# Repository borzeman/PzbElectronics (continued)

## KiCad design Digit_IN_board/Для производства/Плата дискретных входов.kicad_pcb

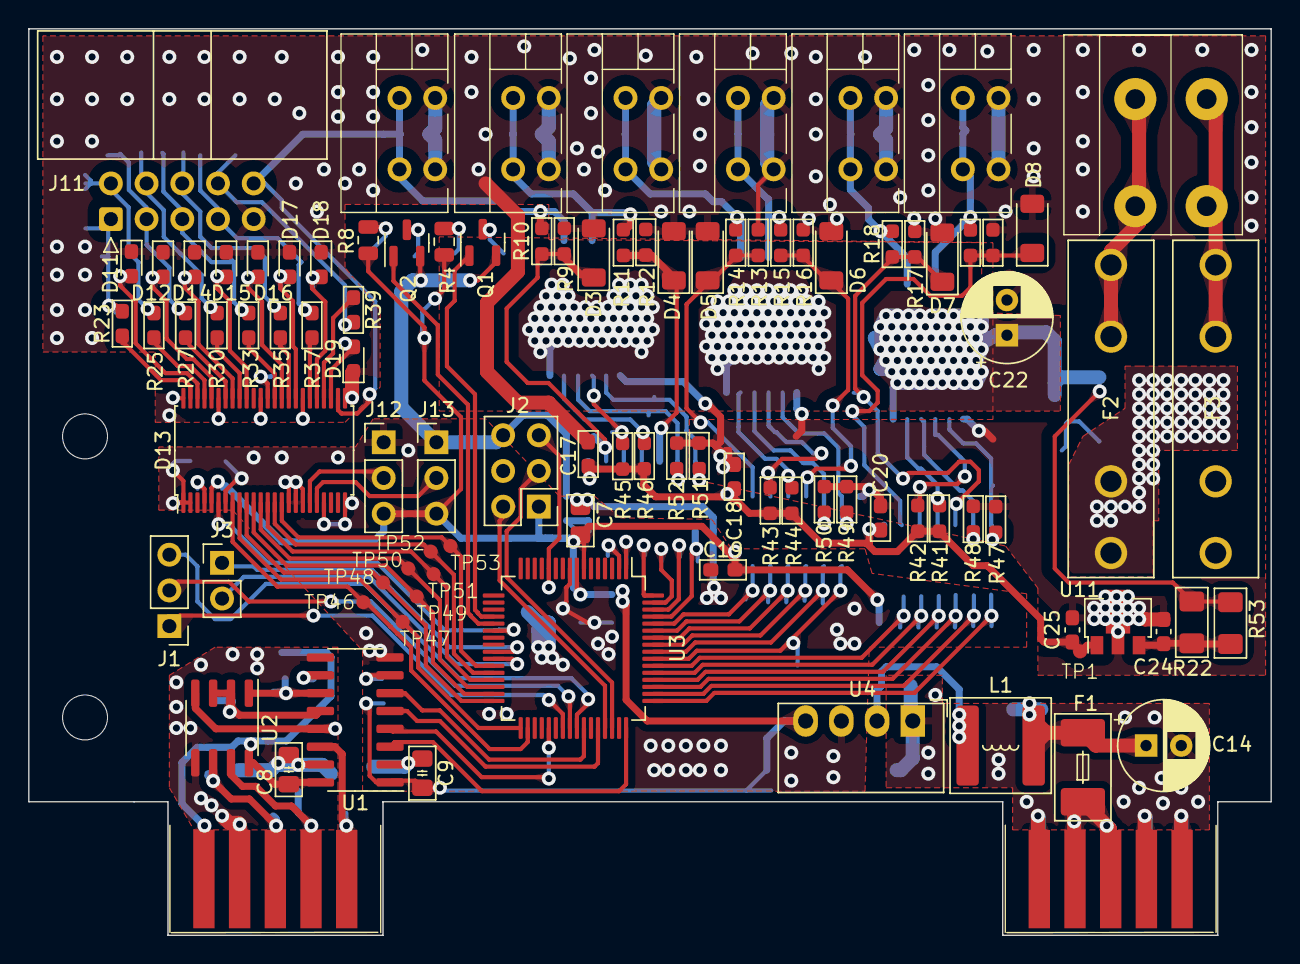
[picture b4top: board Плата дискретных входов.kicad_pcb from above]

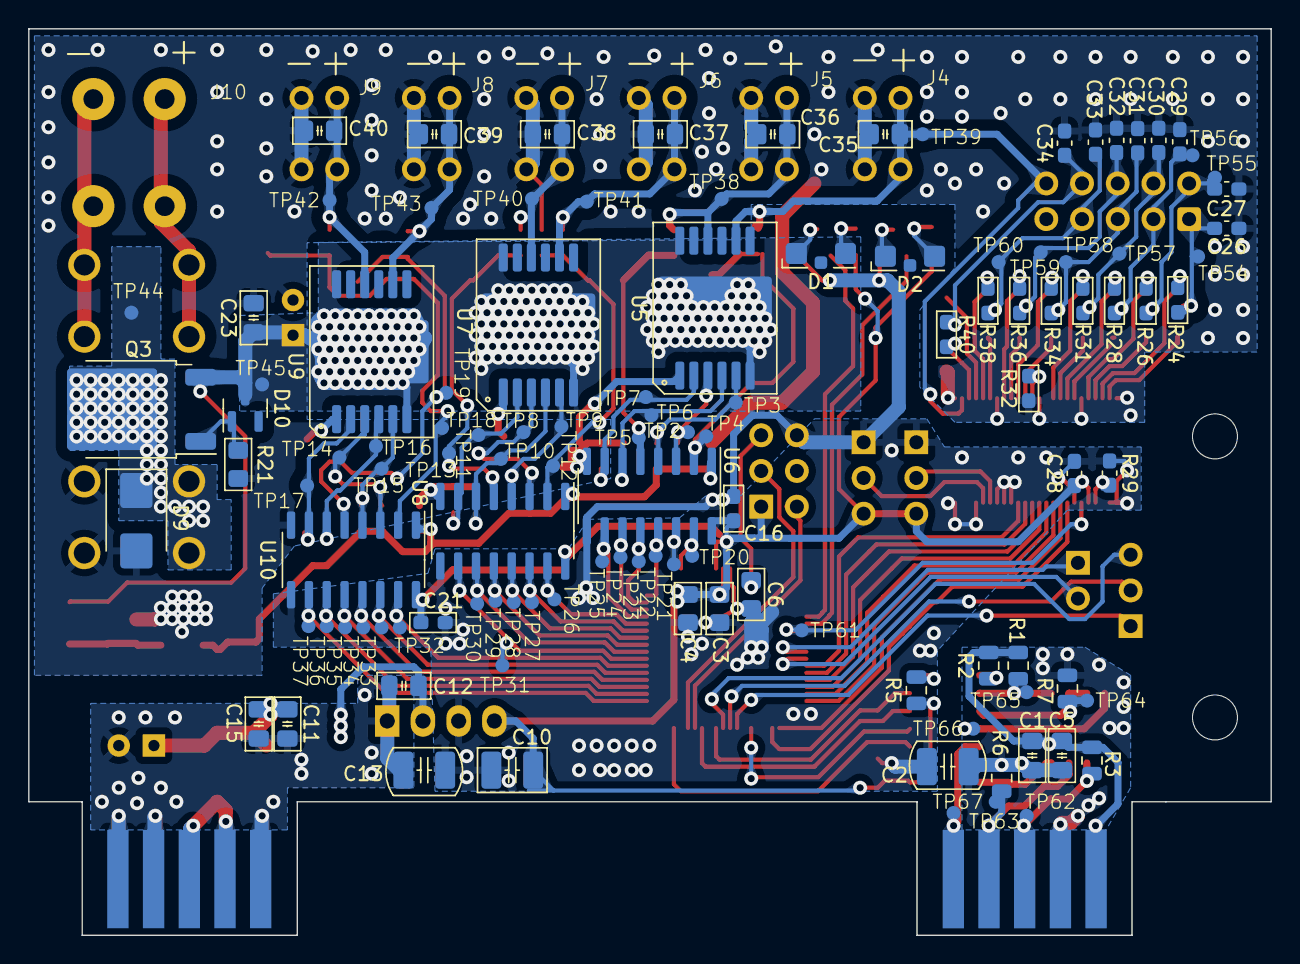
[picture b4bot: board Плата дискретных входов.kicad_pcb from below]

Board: 2 copper layers, 88.4 x 64.5 mm, 214 parts (115 on the bottom side), 121 nets.

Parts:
C1: 1uF 100V 0805; C_0805_2012Metric_Pad1.18x1.45mm_HandSolder
C2, C13: 270 pf X7R 1206 2000v 202R18W271KW4E; C_1210_3225Metric_Pad1.42x2.65mm
C3, C6, C7: 0,1uF 100V 0805; R_0805_2012Metric_Pad1.20x1.40mm_HandSolder
C4: 4,7uF 50V 0805; R_0805_2012Metric_Pad1.20x1.40mm_HandSolder
C5, C8, C9, C15, C23, C35, C36, C37, C38, C39, C40: 0,1uF 100V 0805; C_0805_2012Metric_Pad1.18x1.45mm_HandSolder
C10: 10uF 50V 1210 GRM32ER71H106K; C_1210_3225Metric_Pad1.42x2.65mm_HandSolder
C11, C12: 4,7uF 50V 0805; C_0805_2012Metric_Pad1.18x1.45mm_HandSolder
C14, C22: 47uF 63V D10,5; CP_Radial_D6.3mm_P2.50mm
C16, C17, C18, C19, C20, C21, C25, C26, C27, C29, C30, C31, C32, C33, C34: 0,1uF 100V 0603; C_0603_1608Metric_Pad1.08x0.95mm_HandSolder
C24, C28: 0,33uF 50V 0603; C_0603_1608Metric_Pad1.08x0.95mm_HandSolder
D1, D2: KPA-3010CGCK; LED_Kingbright_KPA-3010_3x2x1mm
D3, D4, D5, D6, D7, D8: BZV55B5V1; D_MiniMELF
D9: SM6T30A (SMB); D_SMB
D10: BZX84C10 (SOT-23); SOT-23
D11, D12, D14, D15, D16, D17, D18, D19: LED 0603 (FYLS-0603UWC); LED_0603_1608Metric_Pad1.05x0.95mm_HandSolder
D13: ISO1I811T; TSSOP-48_6.1x12.5mm_P0.5mm
F1: 045201.5MRL; Fuse_Littelfuse-NANO2-451_453
F2, F3: Fuse 5A ZH266 (2 клипсы); Fuseholder_100_series_5x20mm_D1,5
H1, H2: MountingHole; MountingHole_3.2mm_M3
J1: DebugUSART (PinHeader_01x03_P2.54mm); PinHeader_1x03_P2.54mm_Vertical
J2: Prog (PinHeader_2x03_P2.54mm); PinHeader_2x03_P2.54mm_Vertical
J3: Debug GPIO (PinHeader_01x02_P2.54mm); PinHeader_1x02_P2.54mm_Vertical
J4, J5, J6, J7, J8, J9: DG141R-02
J10: DG142R-5.08-02P-14
J11: DS1013-01-10RSiB-B (1); IDC-Header_2x05_P2.54mm_Horizontal
J12, J13: DS0; PinHeader_1x03_P2.54mm_Vertical
L1: 6,8uH 3,5A ETQP3M6R8KVP; L_Bourns-SRN6028
Q1, Q2: DTC114ECA (SOT-23); SOT-23
Q3: IRFR5305 (TO-252-2); TO-252-2
R1, R7: 0805-10 кОм±5%-0,125 Вт; R_0805_2012Metric
R2, R5: 0805-4,7 кОм±5%-0,125 Вт; R_0805_2012Metric
R3, R6: 0805-560 Ом±5%-0,125 Вт; R_0805_2012Metric
R4, R8: 0805-150 Ом±5%-0,125 Вт; R_0805_2012Metric
R9, R13, R17: 0603-3 кОм±5%-0,062 Вт; R_0603_1608Metric_Pad0.98x0.95mm_HandSolder
R10, R11, R14, R15, R18, R19: 0603-12 кОм±5%-0,062 Вт; R_0603_1608Metric_Pad0.98x0.95mm_HandSolder
R12, R16, R20, R41, R42, R43, R44, R45, R46, R47, R48, R49, R50, R51, R52: 0603-10 кОм±5%-0,062 Вт; R_0603_1608Metric_Pad0.98x0.95mm_HandSolder
R21: 0805-10 кОм±5%-0,125 Вт; R_0805_2012Metric_Pad1.20x1.40mm_HandSolder
R22: 1206-620 Ом±5%-0,25 Вт; R_1206_3216Metric_Pad1.42x1.75mm_HandSolder
R23, R25, R27, R30, R33, R35, R37, R39: 0603-2 кОм±5%-0,062 Вт; R_0603_1608Metric_Pad1.05x0.95mm_HandSolder
R24, R26, R28, R31, R34, R36, R38, R40: 0603-12 кОм±5%-0,062 Вт; R_0603_1608Metric_Pad1.05x0.95mm_HandSolder
R29: 0603-200 кОм±5%-0,062 Вт; C_0603_1608Metric_Pad1.08x0.95mm_HandSolder
R32: 0603-33 Ом±5%-0,062 Вт; R_0603_1608Metric_Pad1.05x0.95mm_HandSolder
R53: OPT; R_1206_3216Metric_Pad1.42x1.75mm_HandSolder
RS1, RS2: SL-10 (L-KLS1-603C-10-S); Edge_Conn_KLS1-603-10
TP1, TP2, TP3, TP4, TP5, TP6, TP7, TP8, TP9, TP10, TP11, TP12, TP13, TP14, TP15, TP16, TP17, TP18, TP19, TP20, TP21, TP22, TP23, TP24, TP25, TP26, TP27, TP28, TP29, TP30, TP31, TP32, TP33, TP34, TP35, TP36, TP37, TP38, TP39, TP40, TP41, TP42, TP43, TP44, TP45, TP46, TP47, TP48, TP49, TP50, TP51, TP52, TP53, TP54, TP55, TP56, TP57, TP58, TP59, TP60, TP61, TP62, TP63, TP64, TP65, TP66, TP67: TestPoint_D1
U1: pia141M30 (SOIC-16); SOIC-16_3.9x9.9mm_P1.27mm
U2: ADM3485EARZ-REEL (SOIC-8); SOIC-8_3.9x4.9mm_P1.27mm
U3: STM32G070RBTx (LQFP-64); LQFP-64_10x10mm_P0.5mm
U4: AM1SS-2403SJZ; Converter_DCDC_Murata_MEE1SxxxxSC_THT
U5: BTS5215 (DSO-12-9); Infineon_PG-DSO-12-9
U6, U8, U10: pia162M30 (SOIC-16); SOIC-16_3.9x9.9mm_P1.27mm
U7, U9: BTS5215; Infineon_PG-DSO-12-9
U11: L78L05 (SOT89-3); SOT-89-3

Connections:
+3V3: C3.1, C4.1, C7.1, C9.2, C10.1, C16.2, C19.2, C21.2, C28.1, D13.5 (VCC), J2.1, J12.3, J13.3, R4.2, R5.1, R8.1, U1.1 (VDD1), U3.7 (VREF+), U3.8 (VDD), U4.4 (OUT+), U6.16 (VDD2), U8.16 (VDD2), U10.16 (VDD2)
+5V: C17.2, C18.2, C20.2, C25.1, R41.1, R42.2, R43.2, R44.1, R45.2, R46.1, TP1.1, U6.1 (VDD1), U8.1 (VDD1), U10.1 (VDD1), U11.1 (OUT)
+24V: C11.1, C14.1, C15.1, F1.2, L1.1
/+3.3VRS485: C1.2, C5.2, C8.2, R1.2, R2.2, R3.2, RS1.1, RS1.10, U1.16 (VDD2), U2.8 (VCC)
/+24_FT_1: C35.2, D13.26 (VBB), J4.2, J11.10, R10.2, TP39.1, U5.8 (OUT2)
/D0: D13.8 (D0), TP46.1, U3.34 (PB14)
/D1: D13.9 (D1), TP47.1, U3.33 (PB13)
/D2: D13.10 (D2), TP48.1, U3.32 (PB12)
/D3: D13.11 (D3), TP49.1, U3.31 (PB11)
/D4: D13.12 (D4), TP50.1, U3.30 (PB10)
/D5: D13.13 (D5), TP51.1, U3.29 (PB2)
/D6: D13.14 (D6), TP52.1, U3.28 (PB1)
/D7: D13.15 (D7), TP53.1, U3.27 (PB0)
/DE_USART_1: U1.5 (VIC), U3.44 (PA12/PA10)
/Descret Input/OUT1_1: C26.1, J11.1, R23.2, R24.1, TP54.1
/Descret Input/OUT1_2: C27.1, J11.2, R25.2, R26.1, TP55.1
/Descret Input/OUT1_3: C29.1, J11.3, R27.2, R28.1, TP56.1
/Descret Input/OUT1_4: C30.1, J11.4, R30.2, R31.1, TP57.1
/Descret Input/OUT1_5: C31.1, J11.5, R33.2, R34.1, TP58.1
/Descret Input/OUT1_6: C32.1, J11.6, R35.2, R36.1, TP59.1
/Descret Input/OUT1_7: C33.1, J11.7, R37.2, R38.1, TP60.1
/Descret Input/OUT1_8: C34.1, J11.8, R39.2, R40.1
/Descret Input/OUT1_H: D13.47 (I7H), R23.1
/Descret Input/OUT1_L: D11.2 (A), D13.46 (I7L), R24.2
/Descret Input/OUT2_H: D13.45 (I6H), R25.1
/Descret Input/OUT2_L: D12.2 (A), D13.44 (I6L), R26.2
/Descret Input/OUT3_H: D13.42 (I5H), R27.1
/Descret Input/OUT3_L: D13.41 (I5L), D14.2 (A), R28.2
/Descret Input/OUT4_H: D13.40 (I4H), R30.1
/Descret Input/OUT4_L: D13.39 (I4L), D15.2 (A), R31.2
/Descret Input/OUT5_H: D13.35 (I3H), R33.1
/Descret Input/OUT5_L: D13.34 (I3L), D16.2 (A), R34.2
/Descret Input/OUT6_H: D13.33 (I2H), R35.1
/Descret Input/OUT6_L: D13.32 (I2L), D17.2 (A), R36.2
/Descret Input/OUT7_H: D13.30 (I1H), R37.1
/Descret Input/OUT7_L: D13.29 (I1L), D18.2 (A), R38.2
/Descret Input/OUT8_H: D13.28 (I0H), R39.1
/Descret Input/OUT8_L: D13.27 (I0L), D19.2 (A), R40.2
/DiscretOut/24V_OUT: C22.1, C23.1, D10.3 (K), Q3.3 (S), R22.2, R53.2, TP45.1, U5.6 (VBB), U5.12 (VBB), U5.13 (VBB), U7.6 (VBB), U7.12 (VBB), U7.13 (VBB), U9.6 (VBB), U9.12 (VBB), U9.13 (VBB)
/DiscretOut/IN1: R52.2, TP6.1, U5.4 (IN2), U6.6 (VOE)
/DiscretOut/IN2: R51.2, TP7.1, U5.2 (IN1), U6.7 (VOF)
/DiscretOut/IN3: R50.2, TP10.1, U7.4 (IN2), U8.6 (VOE)
/DiscretOut/IN4: R49.2, TP11.1, U7.2 (IN1), U8.7 (VOF)
/DiscretOut/IN5: R48.2, TP16.1, U9.4 (IN2), U10.6 (VOE)
/DiscretOut/IN6: R47.2, TP17.1, U9.2 (IN1), U10.7 (VOF)
/DiscretOut/OUT1_1: D3.1 (K), R9.2, R10.1, TP4.1, U6.2 (VIA)
/DiscretOut/OUT2: C36.2, J5.2, R11.2, TP38.1, U5.10 (OUT1)
/DiscretOut/OUT2_1: D4.1 (K), R11.1, R12.2, TP5.1, U6.5 (VID)
/DiscretOut/OUT3: C37.2, J6.2, R14.2, TP41.1, U7.8 (OUT2)
/DiscretOut/OUT3_1: D5.1 (K), R13.2, R14.1, TP12.1, U8.2 (VIA)
/DiscretOut/OUT4: C38.2, J7.2, R15.2, TP40.1, U7.10 (OUT1)
/DiscretOut/OUT4_1: D6.1 (K), R15.1, R16.2, TP13.1, U8.5 (VID)
/DiscretOut/OUT5: C39.2, J8.2, R18.2, TP43.1, U9.8 (OUT2)
/DiscretOut/OUT5_1: D7.1 (K), R17.2, R18.1, TP19.1, U10.5 (VID)
/DiscretOut/OUT6: C40.2, J9.2, R19.2, TP42.1, U9.10 (OUT1)
/DiscretOut/OUT6_1: D8.1 (K), R19.1, R20.2, TP18.1, U10.2 (VIA)
/DiscretOut/ST1: R46.2, TP3.1, U5.5 (ST2), U6.4 (VIC)
/DiscretOut/ST2: R45.1, TP2.1, U5.3 (ST1), U6.3 (VIB)
/DiscretOut/ST3: R44.2, TP9.1, U7.5 (ST2), U8.4 (VIC)
/DiscretOut/ST4: R43.1, TP8.1, U7.3 (ST1), U8.3 (VIB)
/DiscretOut/ST5: R41.2, TP15.1, U9.5 (ST2), U10.4 (VIC)
/DiscretOut/ST6: R42.1, TP14.1, U9.3 (ST1), U10.3 (VIB)
/ERR: D13.6 (/ERR), TP61.1, U3.22 (PA5)
/GPIO1: J3.1, U3.25 (PC4)
/GPIO2: J3.2, U3.26 (PC5)
/NRST: C6.1, J2.5, U3.12 (NRST)
/ON_OUT1: TP24.1, U3.62 (PB8), U6.11 (VIE)
/ON_OUT2: TP25.1, U3.61 (PB7), U6.10 (VIF)
/ON_OUT3: TP30.1, U3.56 (PD6), U8.11 (VIE)
/ON_OUT4: TP31.1, U3.55 (PD5), U8.10 (VIF)
/ON_OUT5: TP36.1, U3.50 (PD0), U10.11 (VIE)
/ON_OUT6: TP37.1, U3.49 (PC9), U10.10 (VIF)
/OUT1_1_cont: TP20.1, U3.2 (PC12), U6.15 (VOA)
/OUT2_1_cont: TP23.1, U3.63 (PB9), U6.12 (VOD)
/OUT3_1_cont: TP26.1, U3.60 (PB6), U8.15 (VOA)
/OUT4_1_cont: TP29.1, U3.57 (PB3), U8.12 (VOD)
/OUT5_1_cont: TP35.1, U3.51 (PD1), U10.12 (VOD)
/OUT6_1_cont: TP33.1, U3.53 (PD3), U10.14 (VOB)
/RTS: RS1.5, RS1.6, TP67.1, U1.14 (VOA)
/RTS_cont: U1.3 (VIA), U3.48 (PC8)
/RX_USART_1: U1.6 (VOD), U3.42 (PA10/NC)
/ST1_cont: TP22.1, U3.64 (PC10), U6.13 (VOC)
/ST2_cont: TP21.1, U3.1 (PC11), U6.14 (VOB)
/ST3_cont: TP28.1, U3.58 (PB4), U8.13 (VOC)
/ST4_cont: TP27.1, U3.59 (PB5), U8.14 (VOB)
/ST5_cont: TP34.1, U3.52 (PD2), U10.13 (VOC)
/ST6_cont: TP32.1, U3.54 (PD4), U10.15 (VOA)
/SWCLK: J2.3, U3.46 (PA14)
/SWDIO: J2.2, U3.45 (PA13)
/TX_USART_1: U1.4 (VIB), U3.37 (PA9/NC)
/UART_DE: J1.1, U3.39 (PC7)
/UART_RX: J1.3, U3.41 (PD9)
/UART_TX: J1.2, U3.40 (PD8)
GND1: C1.1, C2.1, C5.1, C8.1, R6.1, R7.1, RS1.2, RS1.9, U1.9 (GND2), U1.15 (GND2), U2.5 (GND)
GND2: C17.1, C18.1, C20.1, C22.2, C23.2, C24.2, C25.2, C26.2, C27.2, C29.2, C30.2, C31.2, C32.2, C33.2, C34.2, C35.1, C36.1, C37.1, C38.1, C39.1, C40.1, D3.2 (A), D4.2 (A), D5.2 (A), D6.2 (A), D7.2 (A), D8.2 (A), D9.2 (A2), D11.1 (K), D12.1 (K), D13.25 (GNDBB), D13.31 (GNDBB), D13.37 (GNDBB), D13.43 (GNDBB), D13.48 (GNDBB), D14.1 (K), D15.1 (K), D16.1 (K), D17.1 (K), D18.1 (K), D19.1 (K), F3.1, J4.1, J5.1, J6.1, J7.1, J8.1, J9.1, J11.9, R9.1, R12.1, R13.1, R16.1, R17.1, R20.1, R21.2, R32.1, R47.1, R48.1, R49.1, R50.1, R51.1, R52.1, U5.1 (GND), U6.8 (GND1), U7.1 (GND), U8.8 (GND1), U9.1 (GND), U10.8 (GND1), U11.2 (GND)
GNDA: C11.2, C12.2, C13.1, C14.2, C15.2, RS2.1, RS2.4, RS2.5, RS2.6, RS2.7, RS2.10, U4.1 (IN-)
GNDD: C2.2, C3.2, C4.2, C6.2, C7.2, C9.1, C10.2, C13.2, C16.1, C19.1, C21.1, C28.2, D13.1 (GND), D13.2 (SEL), D13.7 (GND), D13.16 (/CS), D13.17 (/RD), D13.18 (GND), D13.21 (GND), D13.24 (GND), J2.6, J12.1, J13.1, Q1.2 (E), Q2.2 (E), R29.1, U1.2 (GND1), U1.8 (GND1), U3.9 (VSS), U4.3 (OUT-), U6.9 (GND2), U8.9 (GND2), U10.9 (GND2)
unnamed: D1.2 (A), R4.1
unnamed: D1.1 (K), Q1.3 (C)
unnamed: D2.2 (A), R8.2
unnamed: D2.1 (K), Q2.3 (C)
unnamed: D9.1 (A1), F2.1, Q3.2 (D), TP44.1
unnamed: D10.1 (A), Q3.1 (G), R21.1
unnamed: D13.19 (DS0), J12.2
unnamed: D13.20 (DS1), J13.2
unnamed: D13.4 (Rosc), R29.2
unnamed: D13.36 (TS), R32.2
unnamed: F2.2, J10.1
unnamed: F3.2, J10.2
unnamed: Q1.1 (B), U3.20 (PA3)
unnamed: Q2.1 (B), U3.21 (PA4)
unnamed: R3.1, RS1.3, RS1.8, TP62.1, U2.6 (A)
unnamed: R6.2, RS1.4, RS1.7, TP63.1, U2.7 (B)
unnamed: F1.1, RS2.2, RS2.3, RS2.8, RS2.9
unnamed: R5.2, U1.7 (VE1)
unnamed: R2.1, U1.10 (VE2)
unnamed: R1.1, TP65.1, U1.11 (VID), U2.1 (RO)
unnamed: TP66.1, U1.13 (VOB), U2.4 (DI)
unnamed: R7.2, TP64.1, U1.12 (VOC), U2.2 (~RE), U2.3 (DE)
unnamed: C12.1, L1.2, U4.2 (IN+)
unnamed: C24.1, R22.1, R53.1, U11.3 (IN)

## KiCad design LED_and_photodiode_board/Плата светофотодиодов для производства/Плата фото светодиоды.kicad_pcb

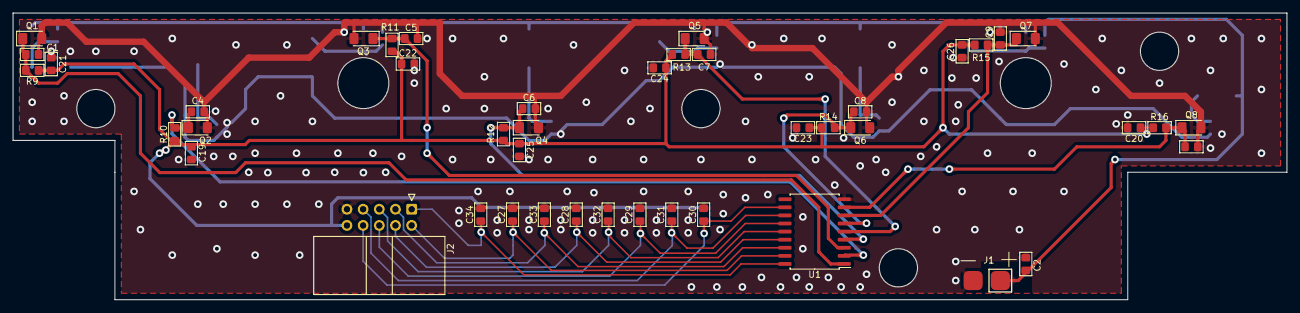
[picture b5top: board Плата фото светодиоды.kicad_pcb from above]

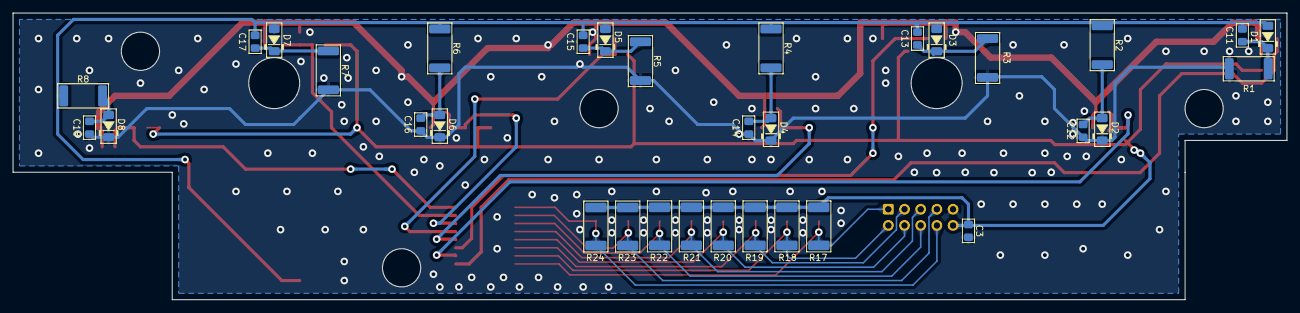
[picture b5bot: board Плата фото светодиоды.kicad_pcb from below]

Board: 2 copper layers, 200.0 x 45.0 mm, 77 parts (33 on the bottom side), 27 nets.

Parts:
C1, C2, C3, C4, C5, C6, C7, C8, C9, C10, C11, C12, C13, C14, C15, C16, C17, C18, C19, C20, C21, C22, C23, C24, C25, C26, C27, C28, C29, C30, C31, C32, C33, C34: 0,1uF 100V 0805; R_0805_2012Metric_Pad1.20x1.40mm_HandSolder
D1, D2, D3, D4, D5, D6, D7, D8: TSML1020; D_MiniMELF
J1: Conn_01x02_Socket; PAD_3x3mm_02
J2: DS1013-01-10RSiB-B; IDC-Header_2x05_P2.54mm_Horizontal
Q1, Q2, Q3, Q4, Q5, Q6, Q7, Q8: PT91-21B/TR7 (1206); D_1206_3216Metric_Pad1.42x1.75mm_HandSolder
R1, R2, R3, R4, R5, R6, R7, R8: 2512-1,2 кОм±5%-1 Вт; R_2512_6332Metric_Pad1.40x3.35mm_HandSolder
R9, R10, R11, R12, R13, R14, R15, R16: 0805-24 кОм±5%-0,125 Вт; R_0805_2012Metric_Pad1.20x1.40mm_HandSolder
R17, R18, R19, R20, R21, R22, R23, R24: 2512-1 кОм±5%-1 Вт; R_2512_6332Metric_Pad1.52x3.35mm_HandSolder
U1: ULN2803A (SOIC-18); SOIC-18W_7.5x11.6mm_P1.27mm

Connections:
/+24_FT_1: C3.1, C19.1, C20.1, C21.1, C22.1, C23.1, C24.1, C25.1, C26.1, J2.10, R9.1, R10.1, R11.1, R12.1, R13.1, R14.1, R15.1, R16.1, R17.2, R18.2, R19.2, R20.2, R21.2, R22.2, R23.2, R24.2
/+24_LED_1: C2.1, C11.1, C13.1, C15.1, C17.1, D1.2 (A), D3.2 (A), D5.2 (A), D7.2 (A), J1.1, R2.1, R4.1, R6.1, R8.1
/OUT1: C34.1, J2.1, R17.1, U1.18 (O1)
/OUT2: C27.1, J2.2, R18.1, U1.17 (O2)
/OUT3: C33.1, J2.3, R19.1, U1.16 (O3)
/OUT4: C28.1, J2.4, R20.1, U1.15 (O4)
/OUT5: C32.1, J2.5, R21.1, U1.14 (O5)
/OUT6: C29.1, J2.6, R22.1, U1.13 (O6)
/OUT7: C31.1, J2.7, R23.1, U1.12 (O7)
/OUT8: C30.1, J2.8, R24.1, U1.11 (O8)
/PhotoTransistor1/OUT: C1.1, Q1.1 (C), R9.2, U1.1 (I1)
/PhotoTransistor2/OUT: C4.1, Q2.1 (C), R10.2, U1.2 (I2)
/PhotoTransistor3/OUT: C5.1, Q3.1 (C), R11.2, U1.3 (I3)
/PhotoTransistor4/OUT: C6.1, Q4.1 (C), R12.2, U1.4 (I4)
/PhotoTransistor5/OUT: C7.1, Q5.1 (C), R13.2, U1.5 (I5)
/PhotoTransistor6/OUT: C8.1, Q6.1 (C), R14.2, U1.6 (I6)
/PhotoTransistor7/OUT: C9.1, Q7.1 (C), R15.2, U1.7 (I7)
/PhotoTransistor8/OUT: C10.1, Q8.1 (C), R16.2, U1.8 (I8)
GNDA: C1.2, C2.2, C3.2, C4.2, C5.2, C6.2, C7.2, C8.2, C9.2, C10.2, C12.2, C14.2, C16.2, C18.2, C19.2, C20.2, C21.2, C22.2, C23.2, C24.2, C25.2, C26.2, C27.2, C28.2, C29.2, C30.2, C31.2, C32.2, C33.2, C34.2, D2.1 (K), D4.1 (K), D6.1 (K), D8.1 (K), J1.2, J2.9, Q1.2 (E), Q2.2 (E), Q3.2 (E), Q4.2 (E), Q5.2 (E), Q6.2 (E), Q7.2 (E), Q8.2 (E), R1.2, R3.2, R5.2, R7.2, U1.9 (GND)
unnamed: C11.2, D1.1 (K), R1.1
unnamed: C12.1, D2.2 (A), R2.2
unnamed: C13.2, D3.1 (K), R3.1
unnamed: C14.1, D4.2 (A), R4.2
unnamed: C15.2, D5.1 (K), R5.1
unnamed: C16.1, D6.2 (A), R6.2
unnamed: C17.2, D7.1 (K), R7.1
unnamed: C18.1, D8.2 (A), R8.2
